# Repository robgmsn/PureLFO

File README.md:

DESIGN STATUS: Awaiting Testing - Ready for beta testing

LFO Updated to V2.2 20/4/21

Traces rerouted.
Trimmers replaced to PTH.
Schmitt Trigger error corrected.

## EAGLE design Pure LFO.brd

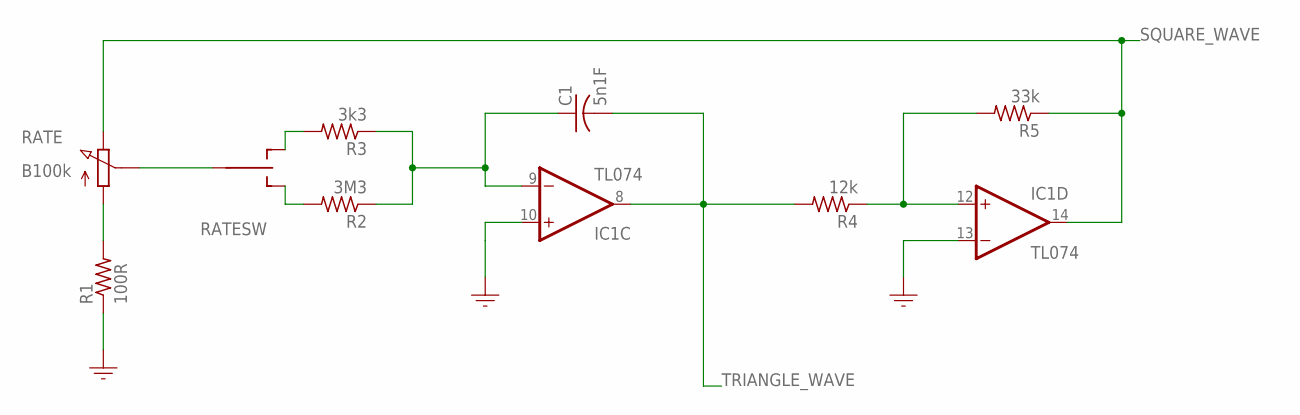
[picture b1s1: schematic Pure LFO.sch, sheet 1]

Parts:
C1: 5n1F; C0805
IC1: TL074; SO14
R1: 100R; R0805
R2: 3M3; R0805
R3: 3k3; R0805
R4: 12k; R0805
R5: 33k; R0805
RATE: B100k; POTENTIOMETER_9MM
RATESW: SWITCH_TOGGLE_SPDT; TOGGLE_SW

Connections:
GND: IC1.10 (+IN), IC1.13 (-IN), R1.1; also elsewhere on the board
unnamed: R1.2, RATE.P$1 (1)
unnamed: RATE.P$2 (2), RATESW.2
unnamed: R3.2, RATESW.1 (O)
unnamed: R2.2, RATESW.3 (S)
unnamed: C1.1, IC1.9 (-IN), R2.1, R3.1
unnamed: IC1.12 (+IN), R4.1, R5.2
SQUARE_WAVE: IC1.14 (OUT), R5.1, RATE.P$3 (3); also elsewhere on the board
TRIANGLE_WAVE: C1.2, IC1.8 (OUT), R4.2; also elsewhere on the board

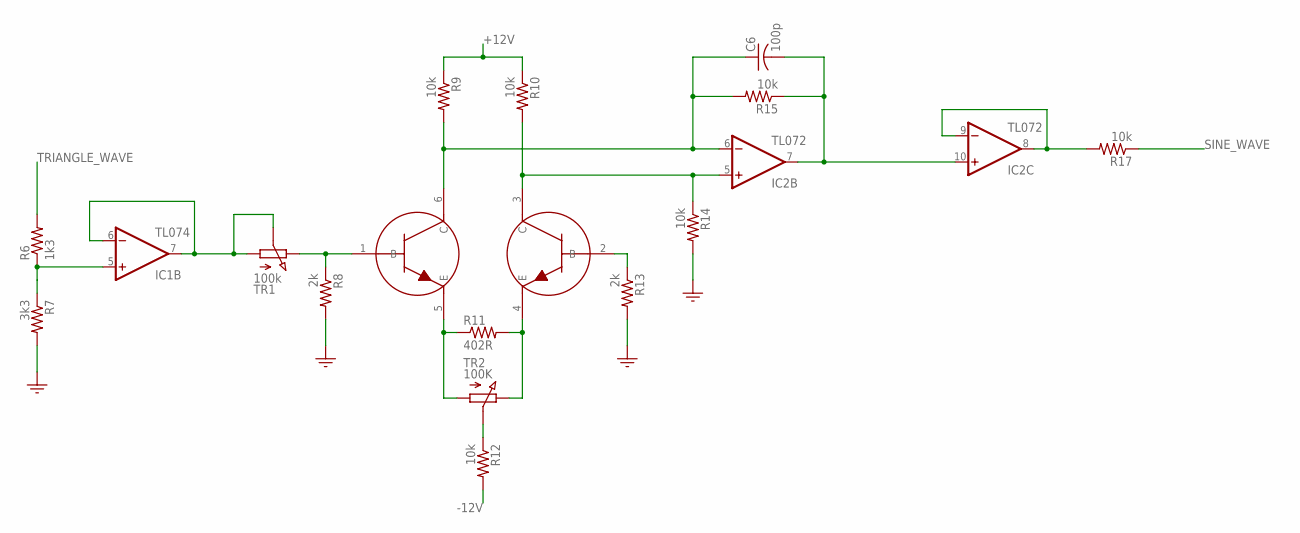
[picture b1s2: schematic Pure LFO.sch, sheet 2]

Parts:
C6: 100p; C0805
IC1: TL074; SO14
IC2: TL072; SO14
R6: 1k3; R0805
R7: 3k3; R0805
R8, R13: 2k; R0805
R9, R10, R12, R14, R15, R17: 10k; R0805
R11: 402R; R0805
T3: DMMT3904W-7-F; TRANS_PAIR
TR1: 100k; TRIMMER_TH
TR2: 100K; TRIMMER_TH

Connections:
+12V: R9.1, R10.1; also elsewhere on the board
-12V: R12.2; also elsewhere on the board
GND: R7.2, R8.2, R13.2, R14.2; also elsewhere on the board
unnamed: IC2.8 (OUT), IC2.9 (-IN), R17.2
unnamed: R11.1, T3.5 (E), TR2.1
unnamed: R8.1, T3.1 (B), TR1.3
unnamed: R11.2, T3.4 (E), TR2.3
unnamed: R12.1, TR2.2
unnamed: R13.1, T3.2 (B)
unnamed: C6.1, IC2.6 (-IN), R9.2, R15.2, T3.6 (C)
unnamed: IC1.6 (-IN), IC1.7 (OUT), TR1.1, TR1.2
unnamed: IC2.5 (+IN), R10.2, R14.1, T3.3 (C)
unnamed: IC1.5 (+IN), R6.1, R7.1
SINE_PRE: C6.2, IC2.7 (OUT), IC2.10 (+IN), R15.1
SINE_WAVE: R17.1; also elsewhere on the board
TRIANGLE_WAVE: R6.2; also elsewhere on the board

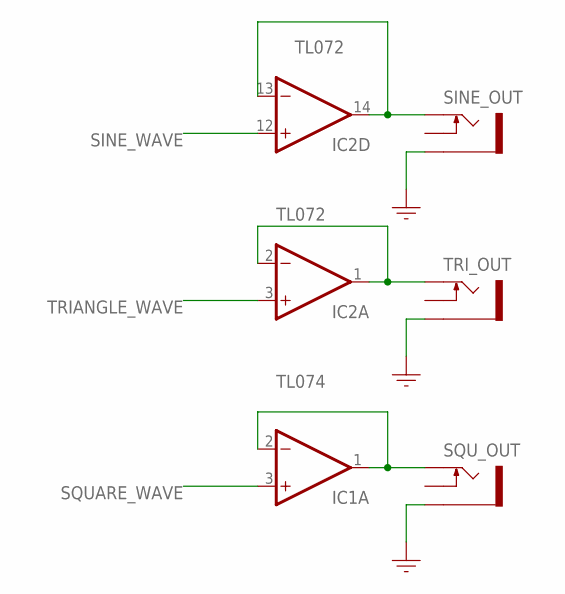
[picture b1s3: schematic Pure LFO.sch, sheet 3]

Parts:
IC1: TL074; SO14
IC2: TL072; SO14
SINE_OUT: SOCKET_MONO_3.5MMPJ301M-12; PJ301M-12
SQU_OUT: SOCKET_MONO_3.5MMPJ301M-12; PJ301M-12
TRI_OUT: SOCKET_MONO_3.5MMPJ301M-12; PJ301M-12

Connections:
GND: SINE_OUT.GND (SLEEVE), SQU_OUT.GND (SLEEVE), TRI_OUT.GND (SLEEVE); also elsewhere on the board
unnamed: IC1.1 (OUT), IC1.2 (-IN), SQU_OUT.TIP
unnamed: IC2.1 (OUT), IC2.2 (-IN), TRI_OUT.TIP
unnamed: IC2.13 (-IN), IC2.14 (OUT), SINE_OUT.TIP
SINE_WAVE: IC2.12 (+IN); also elsewhere on the board
SQUARE_WAVE: IC1.3 (+IN); also elsewhere on the board
TRIANGLE_WAVE: IC2.3 (+IN); also elsewhere on the board

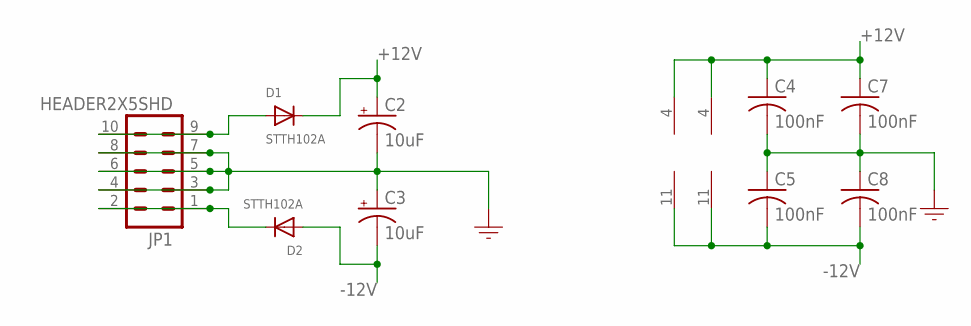
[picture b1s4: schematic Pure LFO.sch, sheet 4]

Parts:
C2, C3: 10uF; 153CLV-0505
C4, C5, C7, C8: 100nF; C0805
D1, D2: STTH102A; SMADIODE
IC1: TL074; SO14
IC2: TL072; SO14
JP1: HEADER2X5SHD; 2X5-SHROUDED

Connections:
+12V: C2.+, C4.1, C7.1, D1.C, IC1.4 (V+), IC2.4 (V+); also elsewhere on the board
-12V: C3.-, C5.2, C8.2, D2.A, IC1.11 (V-), IC2.11 (V-); also elsewhere on the board
GND: C2.-, C3.+, C4.2, C5.1, C7.2, C8.1, JP1.3, JP1.4, JP1.5, JP1.6, JP1.7, JP1.8; also elsewhere on the board
unnamed: D1.A, JP1.9, JP1.10
unnamed: D2.C, JP1.1, JP1.2

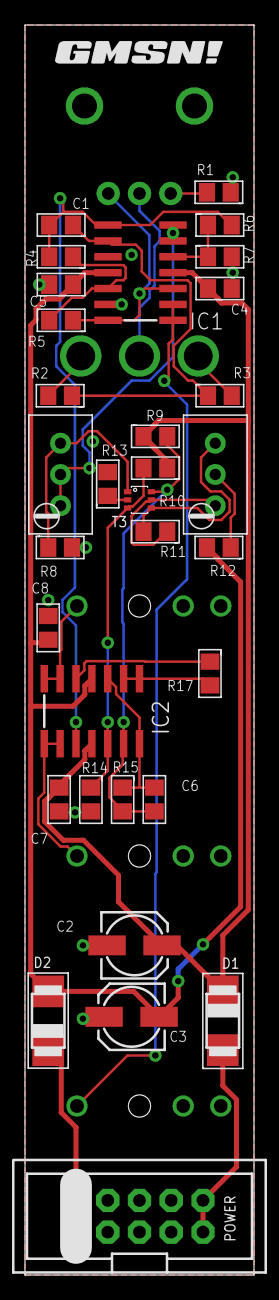
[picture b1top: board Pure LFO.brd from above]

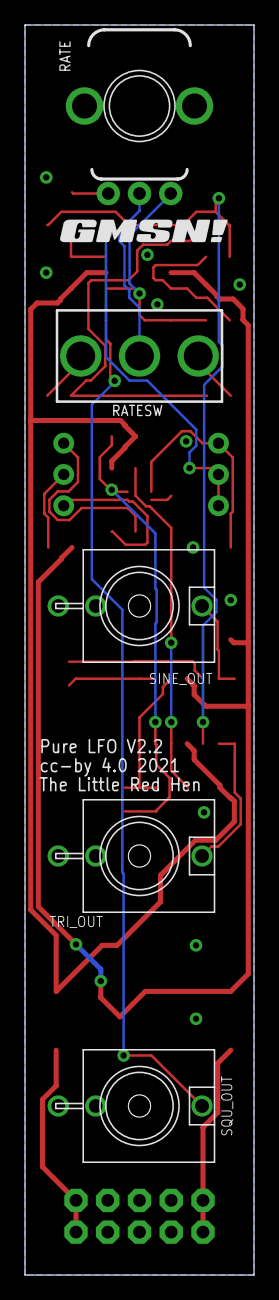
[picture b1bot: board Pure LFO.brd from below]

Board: 2 copper layers, 18.3 x 100.0 mm, 39 parts (6 on the bottom side), 28 nets.

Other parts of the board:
U$1, U$2: GMSN!_LOGO

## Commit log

2021-04-16 LFO 2.0
2021-04-16 LFO 2.1
2021-04-16 Backlink to CADLAB.io has been added.
2021-04-20 LFO 2.2
    LFO Updated to V2.2 20/4/21
    Traces rerouted.
    Schmitt Trigger error corrected.

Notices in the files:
Pure LFO.brd:
cc-by 4.0 2021
